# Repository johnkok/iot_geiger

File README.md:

# IoT Geiger counter
IoT Geiger counter based on NINA-W106 u-blox module.

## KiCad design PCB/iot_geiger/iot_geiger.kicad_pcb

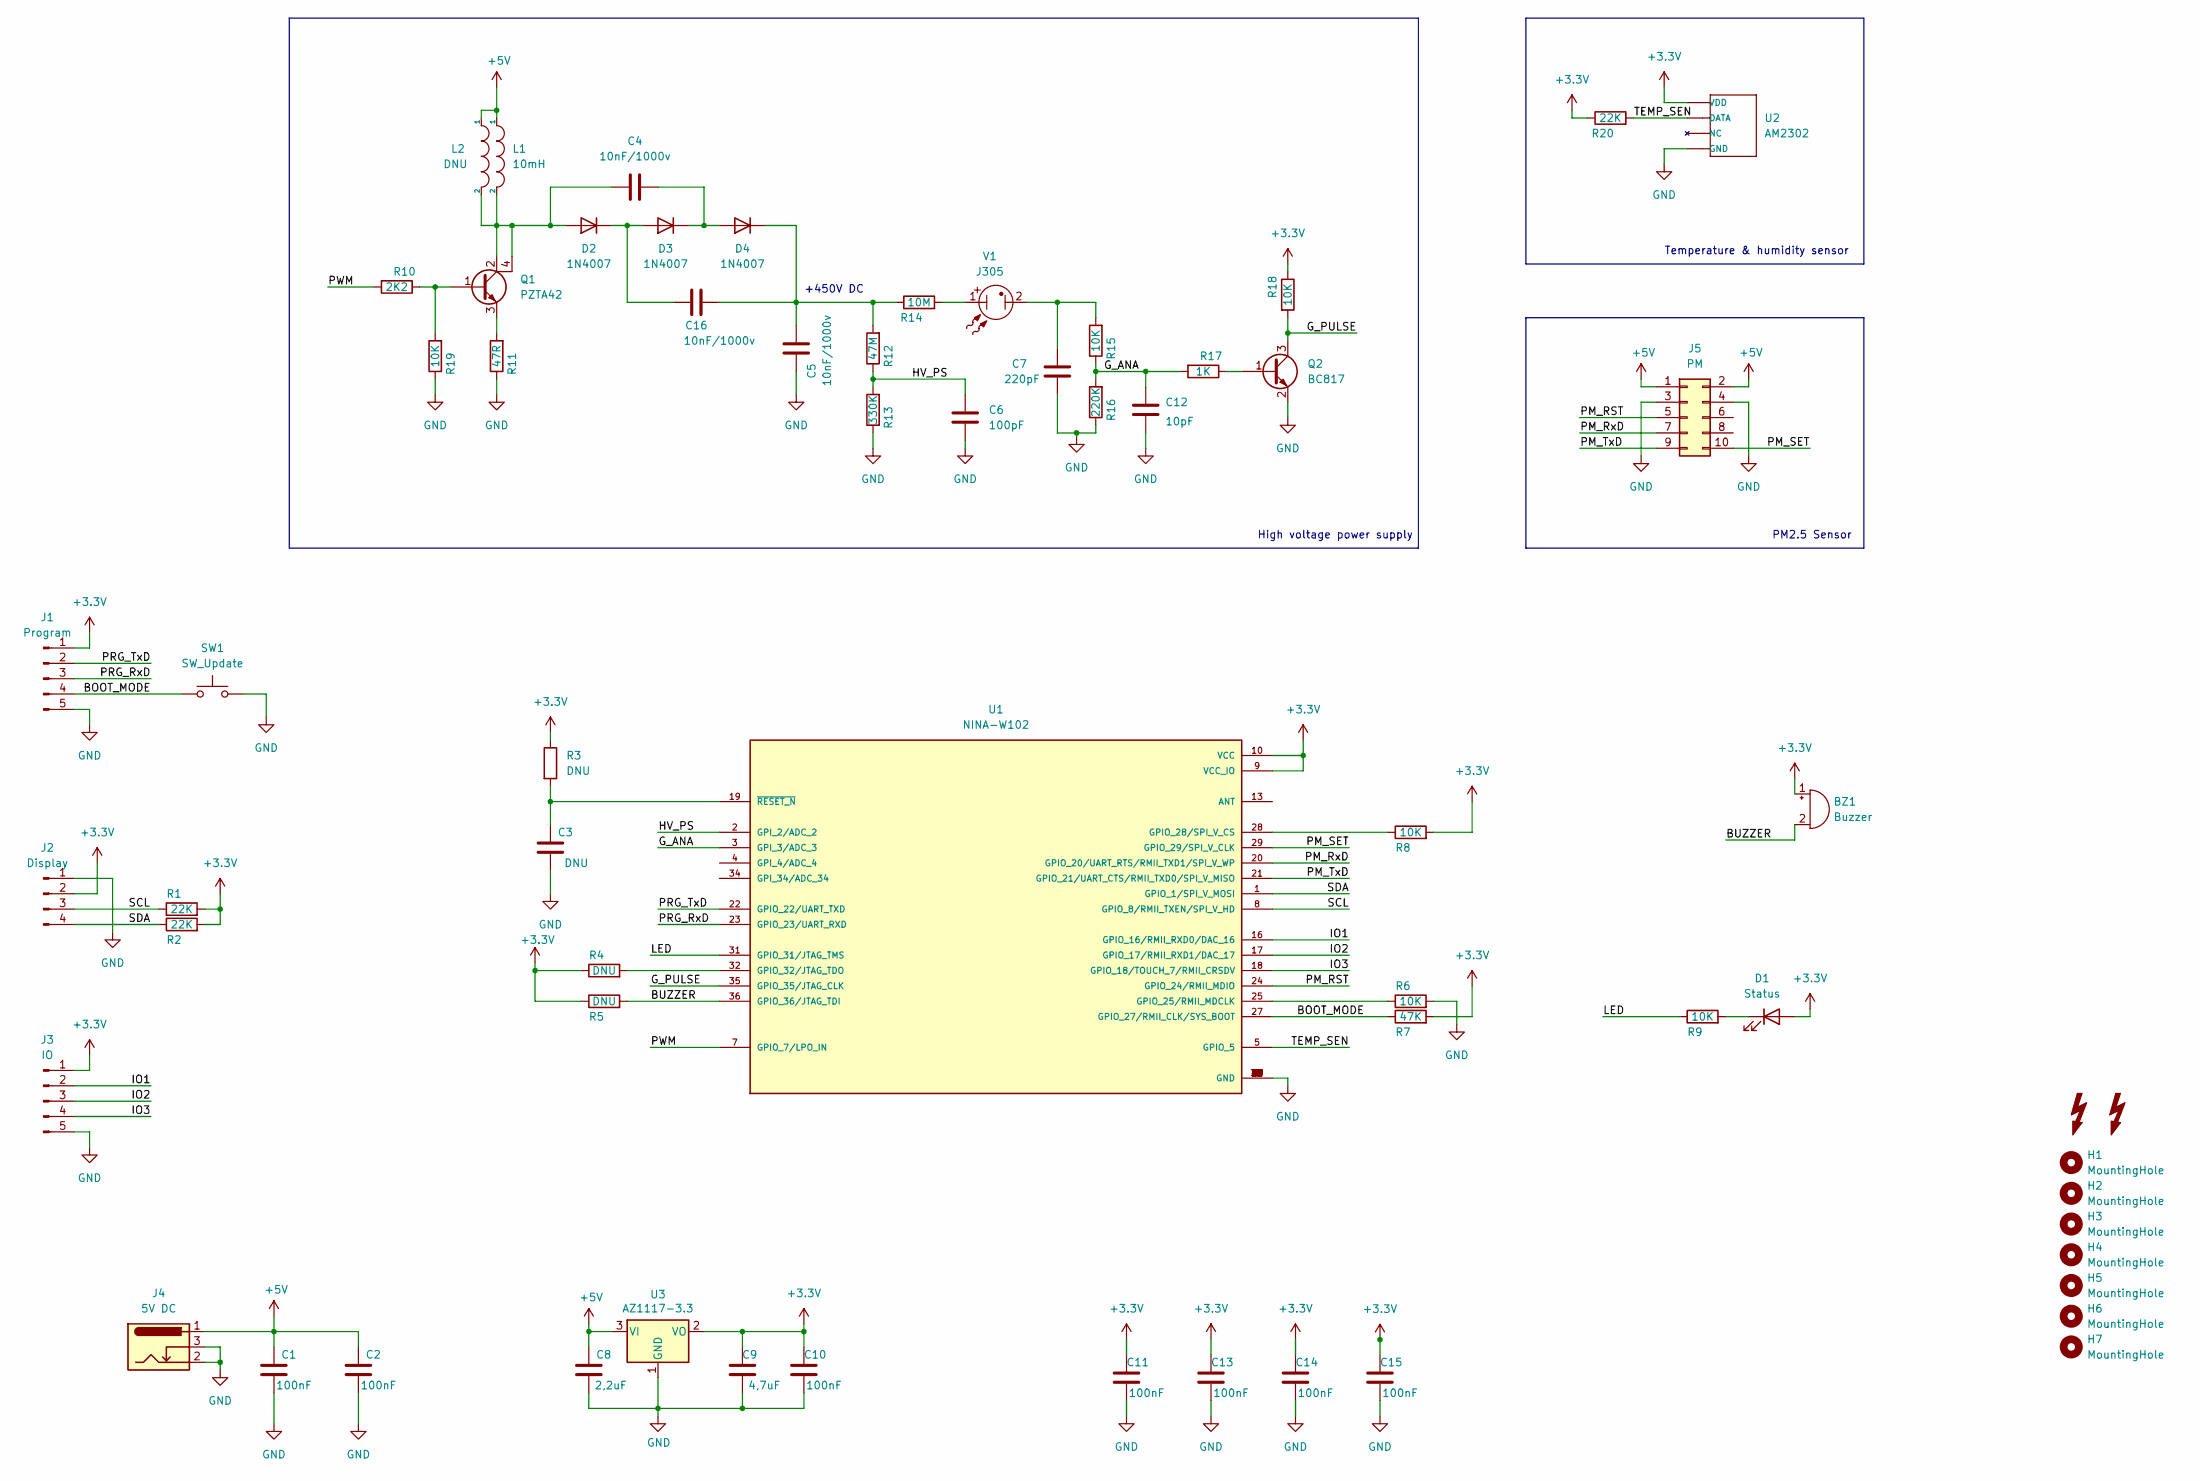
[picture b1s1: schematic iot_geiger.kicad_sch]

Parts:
BZ1: Buzzer; Buzzer_12x9.5RM7.6
C1, C2, C10, C11, C13, C14, C15: 100nF; C_0603_1608Metric
C3: DNU; C_0603_1608Metric
C4, C5, C16: 10nF/1000v; C_Disc_D7.5mm_W2.5mm_P5.00mm
C6: 100pF; C_0603_1608Metric_Pad1.08x0.95mm_HandSolder
C7: 220pF; C_Disc_D9.0mm_W2.5mm_P5.00mm
C8: 2,2uF; C_0603_1608Metric_Pad1.08x0.95mm_HandSolder
C9: 4,7uF; C_0805_2012Metric_Pad1.18x1.45mm_HandSolder
C12: 10pF; C_0603_1608Metric_Pad1.08x0.95mm_HandSolder
D1: Status; LED_0603_1608Metric_Pad1.05x0.95mm_HandSolder
D2, D3, D4: 1N4007; D_DO-41_SOD81_P10.16mm_Horizontal
H1, H2, H3, H4, H5, H6, H7: MountingHole; MountingHole_2.5mm
J1: Program; PinHeader_1x05_P2.54mm_Vertical
J2: Display; PinHeader_1x04_P2.54mm_Vertical
J3: IO; PinHeader_1x05_P2.54mm_Vertical
J4: 5V DC; BarrelJack_GCT_DCJ200-10-A_Horizontal
J5: PM; PinSocket_2x05_P1.27mm_Vertical
L1: 10mH; L_12x12mm_H6mm
L2: DNU; L_Radial_D10.0mm_P5.00mm_Fastron_07M
Q1: PZTA42; SOT-223
Q2: BC817; SOT-23
R1, R2, R20: 22K; R_0603_1608Metric_Pad0.98x0.95mm_HandSolder
R3, R4, R5: DNU; R_0603_1608Metric_Pad0.98x0.95mm_HandSolder
R6, R8, R9, R15, R18, R19: 10K; R_0603_1608Metric_Pad0.98x0.95mm_HandSolder
R7: 47K; R_0603_1608Metric_Pad0.98x0.95mm_HandSolder
R10: 2K2; R_0603_1608Metric_Pad0.98x0.95mm_HandSolder
R11: 47R; R_0603_1608Metric_Pad0.98x0.95mm_HandSolder
R12: 47M; R_Axial_DIN0309_L9.0mm_D3.2mm_P5.08mm_Vertical
R13: 330K; R_0603_1608Metric_Pad0.98x0.95mm_HandSolder
R14: 10M; R_Axial_DIN0309_L9.0mm_D3.2mm_P5.08mm_Vertical
R16: 220K; R_0603_1608Metric_Pad0.98x0.95mm_HandSolder
R17: 1K; R_0603_1608Metric_Pad0.98x0.95mm_HandSolder
S1, S2: SYM_Flash_Small; Symbol_HighVoltage_Type2_CopperTop_VerySmall
SW1: SW_Update; SW_PUSH_6mm_H4.3mm
U1: NINA-W102; XCVR_NINA-W102; PARTREV R05
U2: AM2302; SNR4-2.54-25.0X15.0X7.0MM; MPN AM2302
U3: AZ1117-3.3; SOT-223-3_TabPin2
V1: J305; Geiger

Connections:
+3V3: BZ1.1 (-), C9.2, C10.2, C11.2, C13.2, C14.2, C15.2, D1.2 (A), J1.1, J2.2, J3.1, R1.2, R2.2, R3.1, R4.1, R5.1, R7.2, R8.2, R18.1, R20.1, U1.9 (VCC_IO), U1.10 (VCC), U2.P$1 (VDD), U3.2 (VO)
+5V: C1.2, C2.2, C8.2, J4.1, J5.1, J5.2, L1.1, L2.1, U3.3 (VI)
/BOOT_MODE: J1.4, R7.1, SW1.1, U1.27 (GPIO_27/RMII_CLK/SYS_BOOT)
/BUZZER: BZ1.2 (+), R5.2, U1.36 (GPIO_36/JTAG_TDI)
/G_ANA: C12.2, R15.1, R16.2, R17.2, U1.3 (GPI_3/ADC_3)
/G_PULSE: Q2.3 (C), R18.2, U1.35 (GPIO_35/JTAG_CLK)
/HV_PS: C6.2, R12.1, R13.2, U1.2 (GPI_2/ADC_2)
/IO1: J3.2, U1.16 (GPIO_16/RMII_RXD0/DAC_16)
/IO2: J3.3, U1.17 (GPIO_17/RMII_RXD1/DAC_17)
/IO3: J3.4, U1.18 (GPIO_18/TOUCH_7/RMII_CRSDV)
/LED: R9.1, U1.31 (GPIO_31/JTAG_TMS)
/PM_RST: J5.5, U1.24 (GPIO_24/RMII_MDIO)
/PM_RxD: J5.7, U1.20 (GPIO_20/UART_RTS/RMII_TXD1/SPI_V_WP)
/PM_SET: J5.10, U1.29 (GPIO_29/SPI_V_CLK)
/PM_TxD: J5.9, U1.21 (GPIO_21/UART_CTS/RMII_TXD0/SPI_V_MISO)
/PRG_RxD: J1.3, U1.23 (GPIO_23/UART_RXD)
/PRG_TxD: J1.2, U1.22 (GPIO_22/UART_TXD)
/PWM: R10.2, U1.7 (GPIO_7/LPO_IN)
/SCL: J2.3, R1.1, U1.8 (GPIO_8/RMII_TXEN/SPI_V_HD)
/SDA: J2.4, R2.1, U1.1 (GPIO_1/SPI_V_MOSI)
/TEMP_SEN: R20.2, U1.5 (GPIO_5), U2.P$2 (DATA)
GND: C1.1, C2.1, C3.1, C5.1, C6.1, C7.1, C8.1, C9.1, C10.1, C11.1, C12.1, C13.1, C14.1, C15.1, J1.5, J2.1, J3.5, J4.2, J4.3, J5.3, J5.4, Q2.2 (E), R6.2, R11.1, R13.1, R16.1, R19.1, SW1.2, U1.6 (GND), U1.12 (GND), U1.14 (GND), U1.26 (GND), U1.30 (GND), U1.37 (GND), U1.38 (GND), U1.39 (GND), U1.40 (GND), U1.41 (GND), U1.42 (GND), U1.43 (GND), U1.44 (GND), U1.45 (GND), U1.46 (GND), U1.47 (GND), U1.48 (GND), U2.P$4 (GND), U3.1 (GND)
unnamed: C3.2, R3.2, U1.19 (~RESET_N)
unnamed: C4.1, D2.2 (A), L1.2, L2.2, Q1.2 (C), Q1.4 (C)
unnamed: C4.2, D3.1 (K), D4.2 (A)
unnamed: C7.2, R15.2, V1.2
unnamed: C16.1, D2.1 (K), D3.2 (A)
unnamed: C5.2, C16.2, D4.1 (K), R12.2, R14.1
unnamed: D1.1 (K), R9.2
unnamed: Q1.1 (B), R10.1, R19.2
unnamed: Q1.3 (E), R11.2
unnamed: Q2.1 (B), R17.1
unnamed: R4.2, U1.32 (GPIO_32/JTAG_TDO)
unnamed: R6.1, U1.25 (GPIO_25/RMII_MDCLK)
unnamed: R8.1, U1.28 (GPIO_28/SPI_V_CS)
unnamed: R14.2, V1.1

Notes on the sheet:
PM2.5 Sensor
+450V DC
High voltage power supply
Temperature & humidity sensor

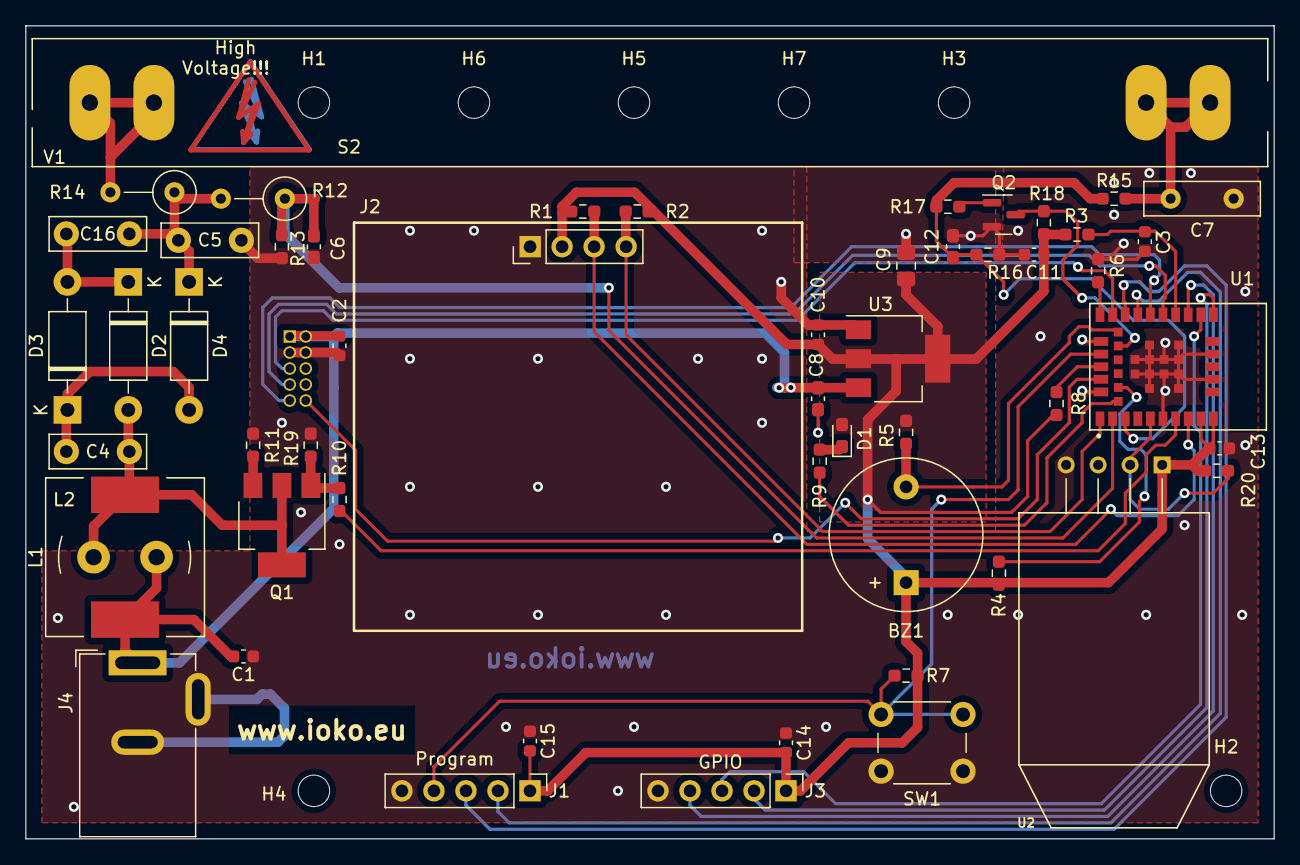
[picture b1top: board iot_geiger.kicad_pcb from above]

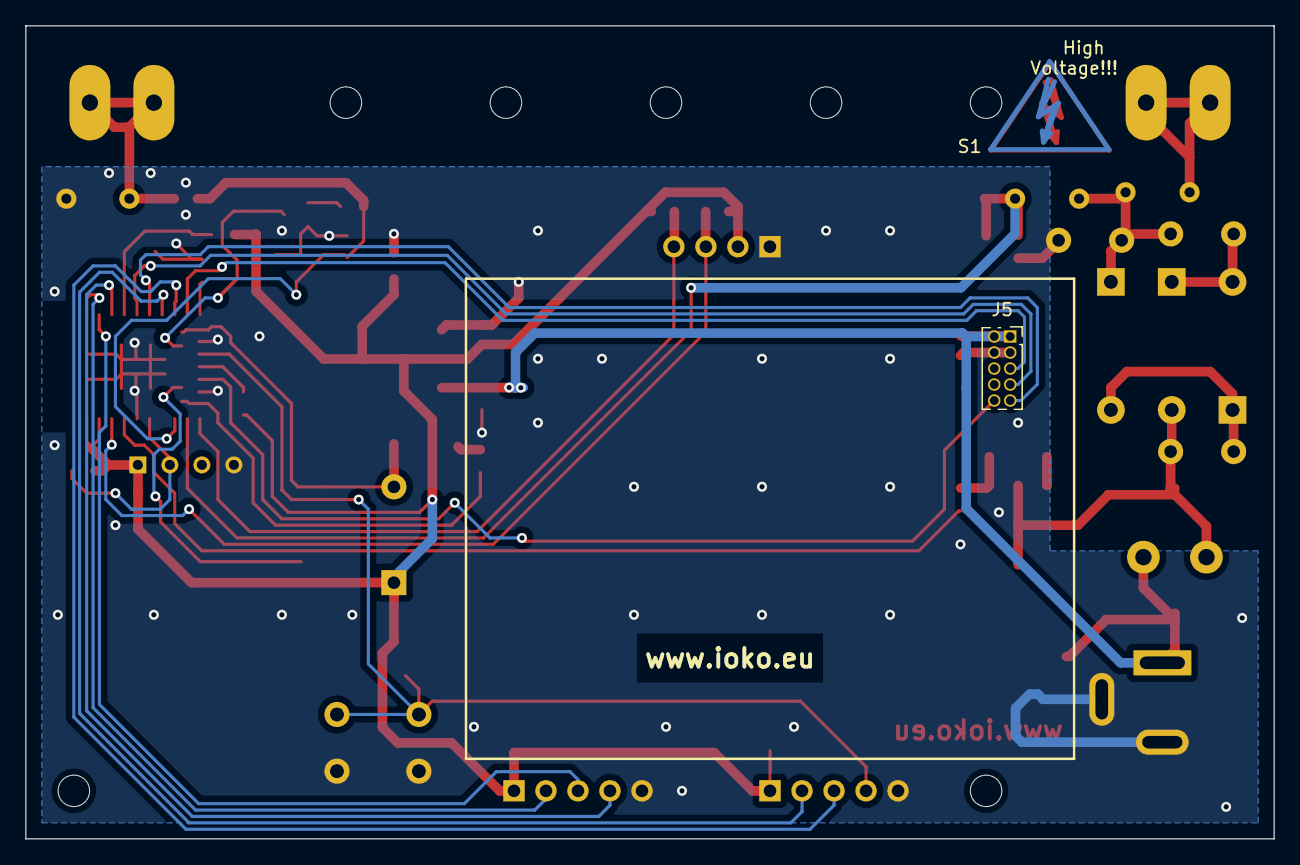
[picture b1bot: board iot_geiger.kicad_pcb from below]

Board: 2 copper layers, 99.1 x 64.5 mm, 64 parts (2 on the bottom side), 36 nets.

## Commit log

2022-04-20 Initial PCB added
2022-04-21 Initial FW added
2022-04-24 fix spiffs
2022-05-05 Add PM sensor support
2022-05-20 PWM added
2022-05-20 PM added
2022-05-20 PCB updated
2022-05-20 Queues added
2022-05-22 AP added
2022-05-24 add webserver
2022-05-24 spiffs added
2022-05-25 mqtt cfg added
2022-05-26 fix wifi sta
2022-05-26 fix mqtt
2022-05-26 fix mqtt topic
2022-06-25 change units to usv/h
2022-11-25 Improve configuration
2022-12-11 Add 3D case files
2022-12-11 add schematic image
